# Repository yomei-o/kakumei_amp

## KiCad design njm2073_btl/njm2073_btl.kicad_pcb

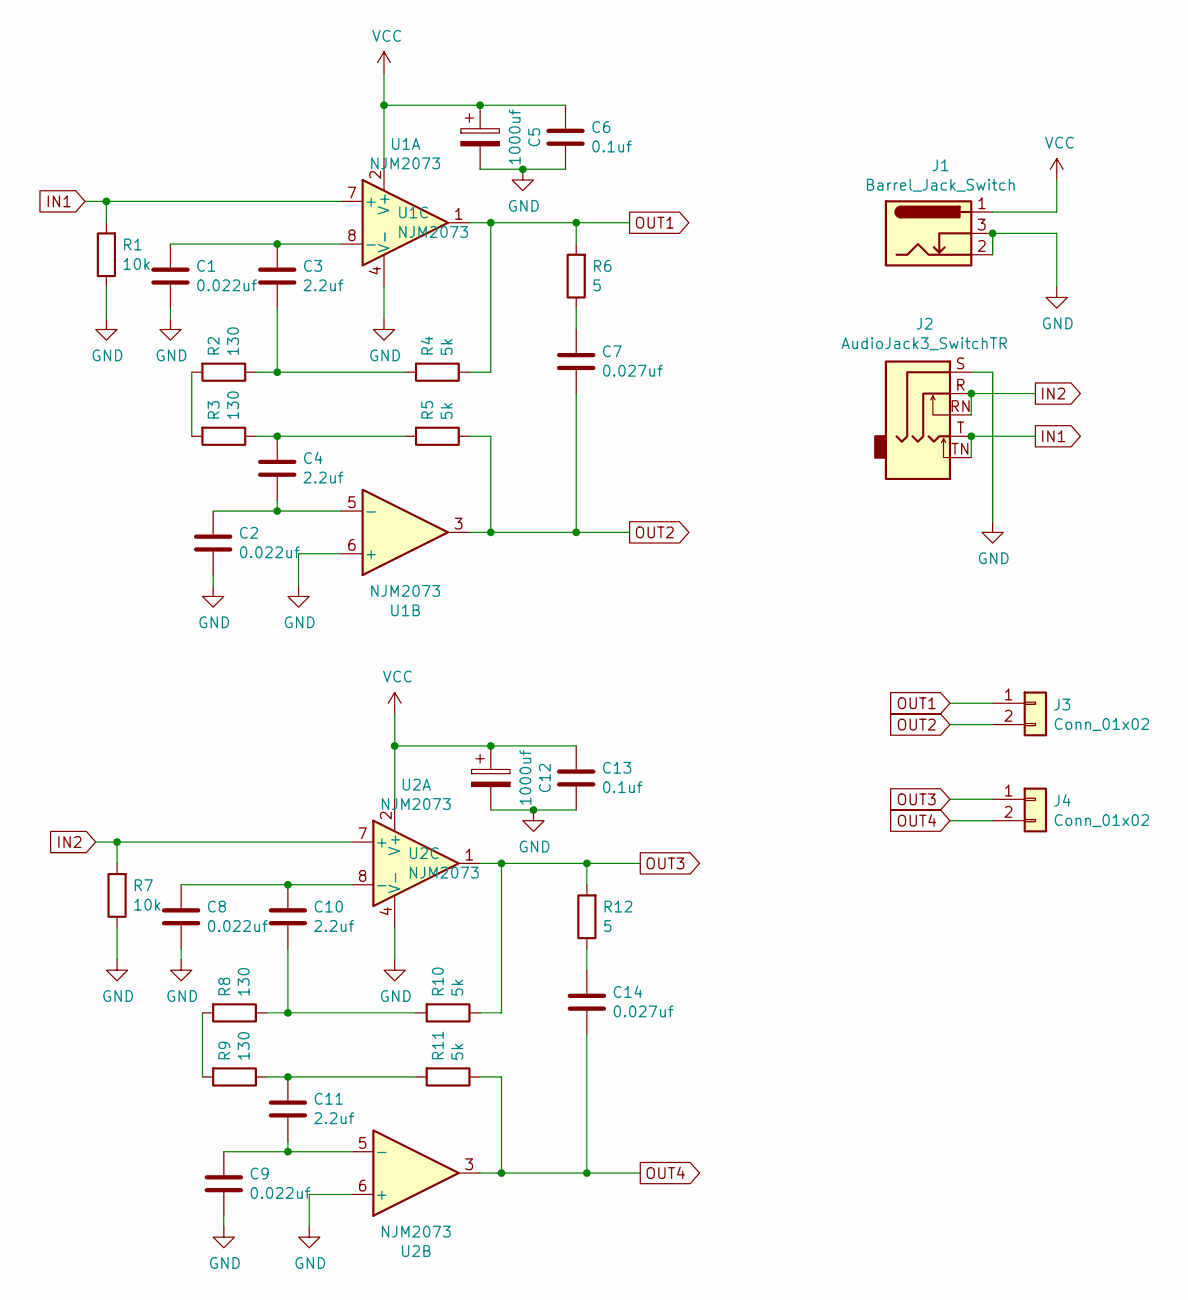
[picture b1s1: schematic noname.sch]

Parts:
C1, C2, C8, C9: 0.022uf; C_Disc_D5.0mm_W2.5mm_P2.50mm
C3, C4, C10, C11: 2.2uf; C_Rect_L10.3mm_W5.0mm_P7.50mm_MKS4
C5, C12: 1000uf; CP_Radial_D10.0mm_P5.00mm
C6, C13: 0.1uf; C_Rect_L7.0mm_W2.0mm_P5.00mm
C7, C14: 0.027uf; C_Rect_L7.0mm_W2.0mm_P5.00mm
J1: Barrel_Jack_Switch; BarrelJack_Horizontal
J2: AudioJack3_SwitchTR; Jack_3.5mm_Ledino_KB3SPRS_Horizontal
J3, J4: Conn_01x02; TerminalBlock_bornier-2_P5.08mm
R1, R7: 10k; R_Axial_DIN0204_L3.6mm_D1.6mm_P7.62mm_Horizontal
R2, R3, R8, R9: 130; R_Axial_DIN0204_L3.6mm_D1.6mm_P7.62mm_Horizontal
R4, R5, R10, R11: 5k; R_Axial_DIN0204_L3.6mm_D1.6mm_P7.62mm_Horizontal
R6, R12: 5; R_Axial_DIN0204_L3.6mm_D1.6mm_P7.62mm_Horizontal
U1, U2: NJM2073; DIP-8_W7.62mm

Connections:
GND: C1.2, C2.2, C5.2, C6.2, C8.2, C9.2, C12.2, C13.2, J1.2, J1.3, J2.S, R1.1, R7.1, U1.4 (V-), U1.6 (+), U2.4 (V-), U2.6 (+)
IN1: J2.T, J2.TN, R1.2, U1.7 (+)
IN2: J2.R, J2.RN, R7.2, U2.7 (+)
unnamed: C1.1, C3.1, U1.8 (-)
unnamed: C2.1, C4.2, U1.5 (-)
unnamed: C3.2, R2.1, R4.2
unnamed: C4.1, R3.1, R5.2
unnamed: C7.1, R6.1
unnamed: C8.1, C10.1, U2.8 (-)
unnamed: C10.2, R8.1, R10.2
unnamed: C11.1, R9.1, R11.2
unnamed: C9.1, C11.2, U2.5 (-)
unnamed: C14.1, R12.1
unnamed: R2.2, R3.2
unnamed: R8.2, R9.2
OUT1: J3.1, R4.1, R6.2, U1.1
OUT2: C7.2, J3.2, R5.1, U1.3
OUT3: J4.1, R10.1, R12.2, U2.1
OUT4: C14.2, J4.2, R11.1, U2.3
VCC: C5.1, C6.1, C12.1, C13.1, J1.1, U1.2 (V+), U2.2 (V+)

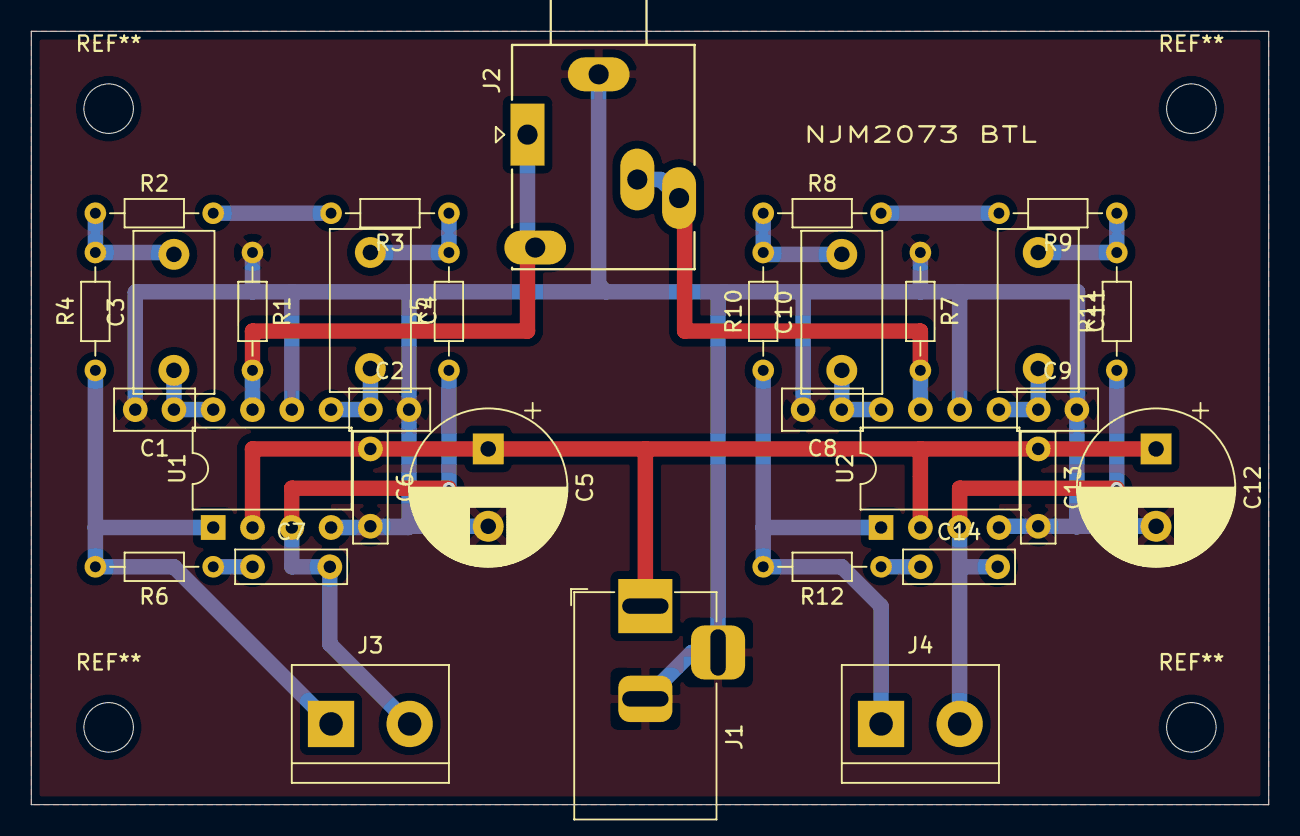
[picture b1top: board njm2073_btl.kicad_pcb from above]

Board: 2 copper layers, 80.0 x 50.0 mm, 32 parts (0 on the bottom side), 20 nets.

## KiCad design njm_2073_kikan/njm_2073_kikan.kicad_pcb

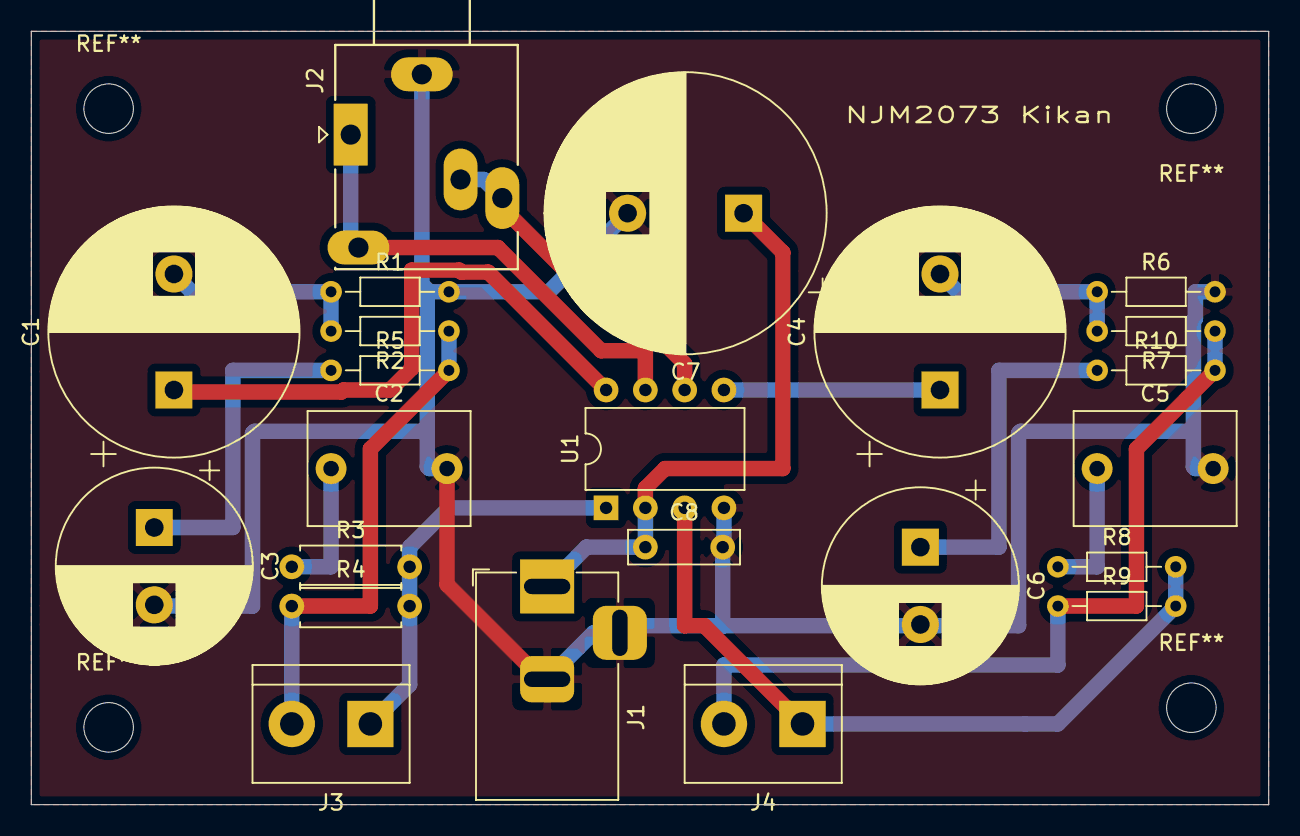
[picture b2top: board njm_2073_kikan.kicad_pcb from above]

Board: 2 copper layers, 80.0 x 50.0 mm, 23 parts (0 on the bottom side), 16 nets.

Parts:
C1, C4: 470uf; CP_Radial_D16.0mm_P7.50mm
C2, C5: 0.22uf; C_Rect_L10.3mm_W7.2mm_P7.50mm_MKS4
C3, C6: 1000uf; CP_Radial_D12.5mm_P5.00mm
C7: 3300uf; CP_Radial_D18.0mm_P7.50mm
C8: 0.1uf; C_Rect_L7.0mm_W2.0mm_P5.00mm
J1: Barrel_Jack_Switch; BarrelJack_Horizontal
J2: AudioJack3_SwitchTR; Jack_3.5mm_Ledino_KB3SPRS_Horizontal
J3, J4: Conn_01x02; TerminalBlock_bornier-2_P5.08mm
R1, R6: 150; R_Axial_DIN0204_L3.6mm_D1.6mm_P7.62mm_Horizontal
R2, R7: 5.1k; R_Axial_DIN0204_L3.6mm_D1.6mm_P7.62mm_Horizontal
R3: 1; R_Axial_DIN0207_L6.3mm_D2.5mm_P7.62mm_Horizontal
R4: 47; R_Axial_DIN0207_L6.3mm_D2.5mm_P7.62mm_Horizontal
R5, R10: 3/1W; R_Axial_DIN0204_L3.6mm_D1.6mm_P7.62mm_Horizontal
R8: 1; R_Axial_DIN0204_L3.6mm_D1.6mm_P7.62mm_Horizontal
R9: 47; R_Axial_DIN0204_L3.6mm_D1.6mm_P7.62mm_Horizontal
U1: NJM2073; DIP-8_W7.62mm

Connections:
GND: C2.2, C3.2, C5.2, C6.2, C7.2, C8.2, J1.2, J1.3, J2.S, R1.2, R6.2, U1.4
IN1: J2.T, J2.TN, U1.7
IN2: J2.R, J2.RN, U1.6
unnamed: C1.1, U1.8
unnamed: C1.2, R1.1, R2.2
unnamed: C2.1, R3.1
unnamed: C3.1, R5.1
unnamed: C4.1, U1.5
unnamed: C4.2, R6.1, R7.2
unnamed: C5.1, R8.1
unnamed: C6.1, R10.1
OUT1: J3.1, R3.2, R4.2, U1.1
OUT2: J3.2, R2.1, R4.1, R5.2
OUT3: J4.1, R8.2, R9.2, U1.3
OUT4: J4.2, R7.1, R9.1, R10.2
VCC: C7.1, C8.1, J1.1, U1.2
